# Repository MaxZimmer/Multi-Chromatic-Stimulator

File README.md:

<p align="right">
<h1 align="center">Multi-Chromatic Stimulator</h1></p>
<h4 align="center">An OpenSource LED stimulator for visual and optogenetics stimulation in combination with 2-photon recording</h4>
<p align="center"><h6 align="right">by M.J.Y. Zimmermann, A.M. Chagas, P. Bartel, T. Baden</h6></p>

This project is licensed under the [GNU General Public License v3.0](https://github.com/MaxZimmer/Multi-Chromatic-Stimulator/blob/master/LICENSE)

The study of colour vision with fluorescence microscopy requires precise control over the spectra of visual stimuli.

Here we describe an effective, low-cost, opensource LED stimulator, designed to be used in combination with a 2-photon microscope. The design is built around an open-source development board and off-the-shelf components. It has been conceived to be assembled and used without the need for advanced electronics skills.

[Instruction Manual](https://github.com/MaxZimmer/Multi-Chromatic-Stimulator/tree/master/Manuscript%20and%20Instruction%20Manual)

***

The following design can control up to 24 spectral channels with 12 bits linear resolution and 25 μs temporal precision. Our system only requires simple electronics components to be assemble and can be combined.
Built around an ESP32 micro-controller an LED driver (Adafruit model) and off-the-shelf components for a total cost of ~$50

***

The stimulator runs synchronous to the recording system using TTL triggers.
TTL signals correspond to scanning mirror retrace periods and are used to turn ON and OFF LEDs, thus avoiding swamping the PMTs by stimulation light.

***

The following design was adjusted for the tetrachromatic zebrafish.
Stimulating LEDs and optical filters were chosen to match the peak sensitivities of opsin spectra while avoiding overlap with the PMT detection bands.

***

In this example, light sources are combined and directed through the onjective.

***

## Repository structure

```
├───3D Designs                                - Contains printed parts for the stimulator and optical components
│   ├───Optical Components
|   |   ├───STL renderings                    - Printing files
|   |   └───SCAD files                        - SCAD files to be modified if need be
│   └───Stimulator
|      ├───STL renderings                    - Printing files
|      └───SCAD files                        - SCAD files to be modified if need be
|
├───Arduino Code
|   ├───Stimulator Code                   - Adaptable C+ code for running the stimulator
|   └───LED drive library                 - Library to run the TLC 5947
|
├───Bill of Materials                         - List of necessary components and retailer suggestions
|
├───Datasheets                                - Contains all technical sheet for:
|   ├───Optical Components                    - ...LEDs, Filters, Dichroic Mirrors used in the presented example
|   ├───Stimulator                            - ...micro-controller and LED driver
|   └───Spectrometer                          - ...device used for calibration
|
├───Images
|
├───Instruction Manual                        - Detailed manual to assemble and calibrate the stimulator
|   └───Stimulator Calibration                - Contains calibration recordings and the adaptable jupyter notebook script to calibrate the stimulator
|       ├───Arduino Calibration Code          - Sequence used for the calibration
|       ├───Filters                           - Filters and dicroic mirrors spectra
|       ├───Powermeter Recording              - Recording of the calibration sequence
|       └───Spectrometer Recording            - Recording of the calibration sequence
|
├───PCB                                       - KiCad and Gerber files to modified and generate PCB for:
│   ├───Potentiometer mounts                  - ...trimmer potentiometers that set the LED maximum brightness
│   └───Stimulator                            - ...the stimulator itself
|
└───References                                - Publication used to design and conceive this model

```

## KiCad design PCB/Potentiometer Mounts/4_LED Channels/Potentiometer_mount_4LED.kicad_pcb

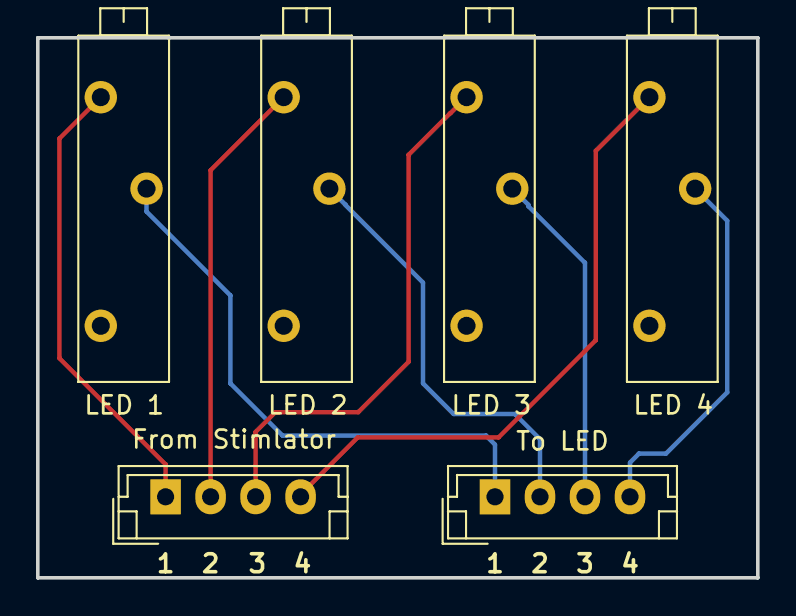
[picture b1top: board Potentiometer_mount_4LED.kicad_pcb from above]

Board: 2 copper layers, 40.0 x 30.0 mm, 6 parts (0 on the bottom side), 8 nets.

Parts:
From Stimlator: JST_EH_B04B-EH-A_1x04_P2.50mm_Vertical
LED 1, LED 2, LED 3, LED 4: Potentiometer_Vishay_43_Horizontal
To LED: JST_EH_B04B-EH-A_1x04_P2.50mm_Vertical

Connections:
unnamed: From Stimlator.1, LED 1.3
unnamed: From Stimlator.2, LED 2.3
unnamed: From Stimlator.3, LED 3.3
unnamed: From Stimlator.4, LED 4.3
unnamed: LED 1.2, To LED.1
unnamed: LED 2.2, To LED.2
unnamed: LED 3.2, To LED.3
unnamed: LED 4.2, To LED.4

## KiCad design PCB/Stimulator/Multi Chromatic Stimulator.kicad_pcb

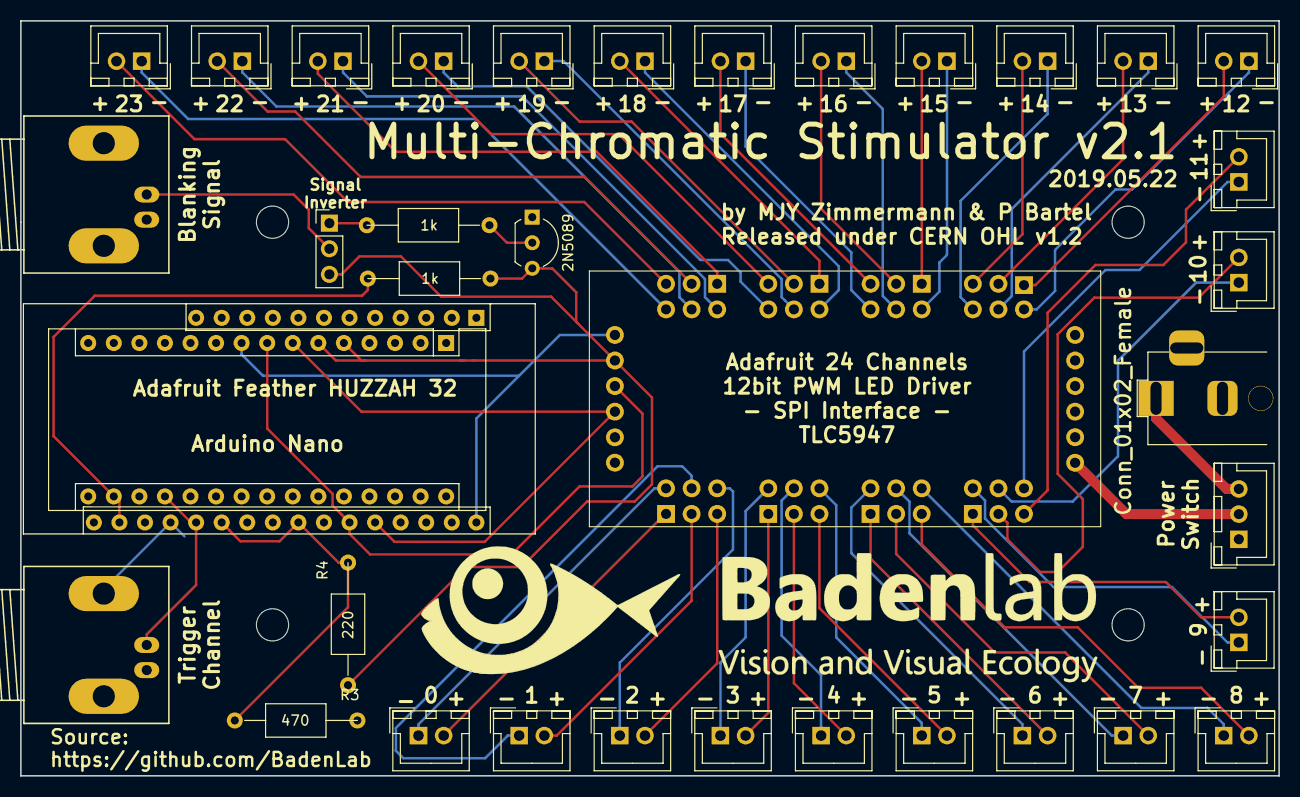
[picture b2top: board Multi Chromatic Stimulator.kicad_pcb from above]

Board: 2 copper layers, 125.0 x 75.0 mm, 4 parts (0 on the bottom side), 2 nets.

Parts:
2N5089: TO-92L_Inline_Wide
J2: Conn_01x02_Female; BarrelJack_Horizontal_maxime
R3: 470; R_Axial_DIN0309_L9.0mm_D3.2mm_P15.24mm_Horizontal
R4: 220; R_Axial_DIN0309_L9.0mm_D3.2mm_P15.24mm_Horizontal

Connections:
GNDREF: 2N5089.1, R3.1
unnamed: R3.2, R4.1

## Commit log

2019-02-09 Create test
2019-02-09 v2.1
2019-02-24 v2.0
2019-03-12 3D files for LED Holder
2019-03-14 Datasheet update
2019-03-14 Update Datasheet
2019-03-14 Update BoM
2019-03-22 3D Design update
2019-04-23 Spectrum Calibration update
2019-04-23 References update
2019-04-25 25/04/2019 update
2019-04-25 Calibration Script Update
2019-05-23 2019.05.23
2019-06-13 2019.06.16 update
2019-07-31 Version 2.1 update

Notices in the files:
PCB/Stimulator/Multi Chromatic Stimulator.kicad_pcb:
Released under CERN OHL v1.2
